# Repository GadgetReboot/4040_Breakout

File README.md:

# 4040_Breakout
CD4040 Ripple Carry Binary Counter/Divider breakout board
<br><br><BR><BR>

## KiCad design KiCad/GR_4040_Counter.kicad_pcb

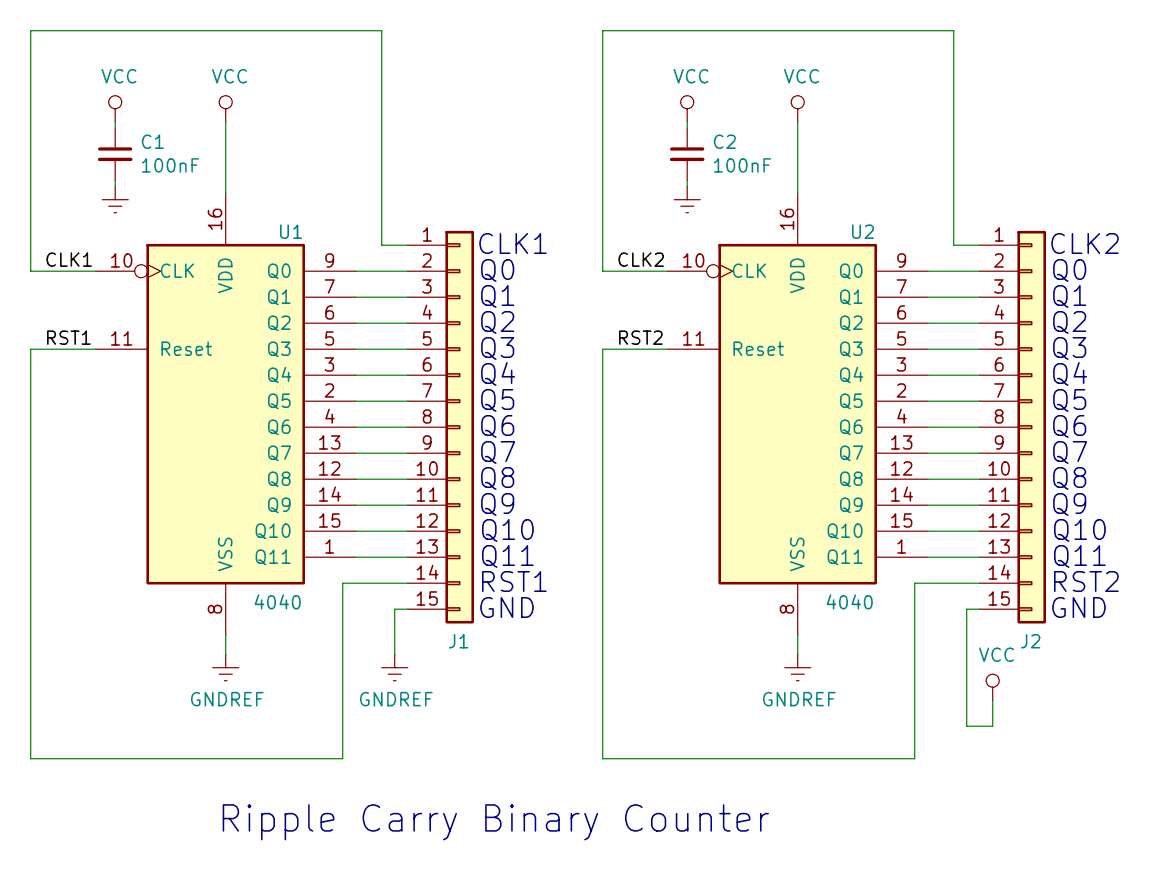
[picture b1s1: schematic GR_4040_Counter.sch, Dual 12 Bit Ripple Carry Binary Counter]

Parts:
C1, C2: 100nF; C_0805_2012Metric_Pad1.15x1.40mm_HandSolder
J1, J2: Conn_01x15; PinHeader_1x15_P2.54mm_Vertical
U1, U2: 4040; SOIC-16_3.9x9.9mm_P1.27mm

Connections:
/CLK1: J1.1, U1.10 (CLK)
/CLK2: J2.1, U2.10 (CLK)
/RST1: J1.14, U1.11 (Reset)
/RST2: J2.14, U2.11 (Reset)
GNDREF: C1.2, C2.2, J1.15, U1.8 (VSS), U2.8 (VSS)
unnamed: J1.2, U1.9 (Q0)
unnamed: J1.3, U1.7 (Q1)
unnamed: J1.4, U1.6 (Q2)
unnamed: J1.5, U1.5 (Q3)
unnamed: J1.6, U1.3 (Q4)
unnamed: J1.7, U1.2 (Q5)
unnamed: J1.8, U1.4 (Q6)
unnamed: J1.9, U1.13 (Q7)
unnamed: J1.10, U1.12 (Q8)
unnamed: J1.11, U1.14 (Q9)
unnamed: J1.12, U1.15 (Q10)
unnamed: J1.13, U1.1 (Q11)
unnamed: J2.2, U2.9 (Q0)
unnamed: J2.3, U2.7 (Q1)
unnamed: J2.4, U2.6 (Q2)
unnamed: J2.5, U2.5 (Q3)
unnamed: J2.6, U2.3 (Q4)
unnamed: J2.7, U2.2 (Q5)
unnamed: J2.8, U2.4 (Q6)
unnamed: J2.9, U2.13 (Q7)
unnamed: J2.10, U2.12 (Q8)
unnamed: J2.11, U2.14 (Q9)
unnamed: J2.12, U2.15 (Q10)
unnamed: J2.13, U2.1 (Q11)
VCC: C1.1, C2.1, J2.15, U1.16 (VDD), U2.16 (VDD)

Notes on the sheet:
Ripple Carry Binary Counter
CLK1
Q10
Q11
RST1
GND
CLK2
RST2

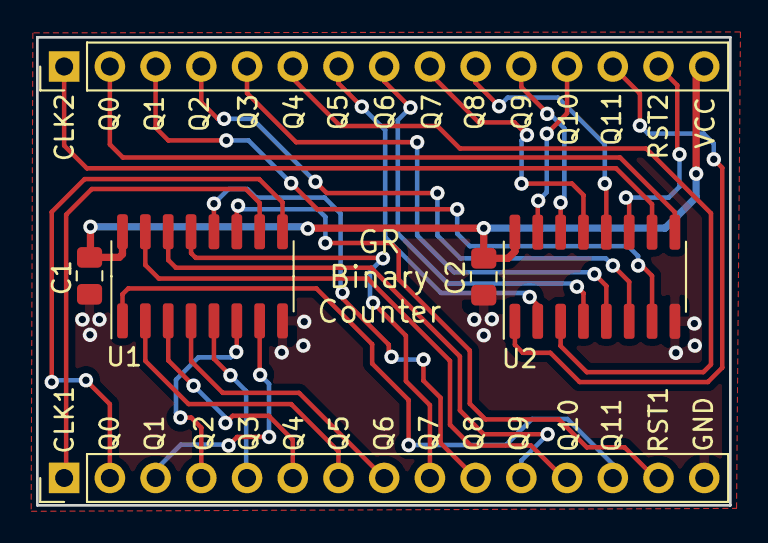
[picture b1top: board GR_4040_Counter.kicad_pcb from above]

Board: 2 copper layers, 38.5 x 26.0 mm, 6 parts (0 on the bottom side), 30 nets.
